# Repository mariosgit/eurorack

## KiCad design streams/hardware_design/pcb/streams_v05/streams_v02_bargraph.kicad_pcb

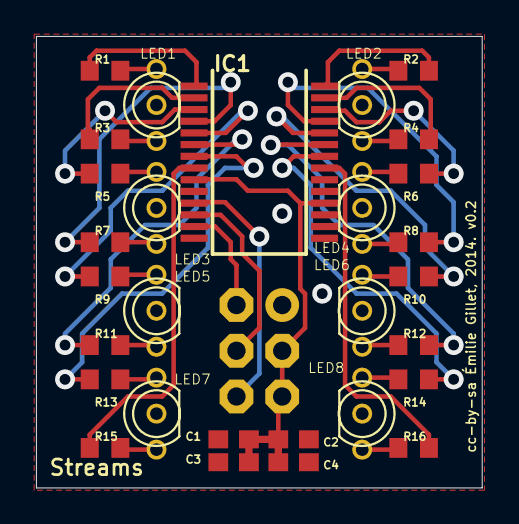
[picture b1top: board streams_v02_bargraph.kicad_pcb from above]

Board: 2 copper layers, 24.8 x 25.1 mm, 30 parts (1 on the bottom side), 37 nets.

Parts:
C1: 100n; C0603
C2, C3, C4: 3.3u; C0603
IC1: MCP23S17SS; SSOP28
JP1: 2X3
LED1, LED2, LED3, LED4, LED5, LED6, LED7, LED8: WP115VEGW; LED-BICOLOR-THROUGHHOLE
R1, R2, R3, R4, R5, R6, R7, R8, R9, R10, R11, R12, R13, R14, R15, R16: 150; R0603

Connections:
+3V3_BARGRAPH: C1.1, C2.1, C3.1, C4.1, IC1.9, IC1.18, JP1.3, JP1.5
GND2: C1.2, C2.2, C3.2, C4.2, IC1.10, IC1.15, IC1.16, IC1.17, JP1.1, LED1.2, LED2.2, LED3.2, LED4.2, LED5.2, LED6.2, LED7.2, LED8.2
unnamed: IC1.11, JP1.6
unnamed: IC1.12, JP1.4
unnamed: LED1.3, R1.2
unnamed: IC1.13, JP1.2
unnamed: LED1.1, R3.2
unnamed: LED3.3, R5.2
unnamed: LED3.1, R7.2
unnamed: LED5.3, R9.2
unnamed: LED5.1, R11.2
unnamed: LED7.3, R13.2
unnamed: LED7.1, R15.2
unnamed: LED8.3, R16.2
unnamed: LED8.1, R14.2
unnamed: LED6.3, R12.2
unnamed: LED6.1, R10.2
unnamed: LED4.3, R8.2
unnamed: LED4.1, R6.2
unnamed: LED2.3, R4.2
unnamed: LED2.1, R2.2
unnamed: IC1.27, R4.1
unnamed: IC1.28, R2.1
unnamed: IC1.1, R1.1
unnamed: IC1.2, R3.1
unnamed: IC1.21, R16.1
unnamed: IC1.22, R14.1
unnamed: IC1.23, R12.1
unnamed: IC1.24, R10.1
unnamed: IC1.25, R8.1
unnamed: IC1.26, R6.1
unnamed: IC1.3, R5.1
unnamed: IC1.4, R7.1
unnamed: IC1.5, R9.1
unnamed: IC1.6, R11.1
unnamed: IC1.7, R13.1
unnamed: IC1.8, R15.1

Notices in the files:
streams/hardware_design/pcb/streams_v05/streams_v02_bargraph.kicad_pcb:
cc-by-sa Émilie Gillet, 2014. v0.2
